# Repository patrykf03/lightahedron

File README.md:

# Lightahedron
This is the project files for the Lightahedron which is a wireless rgb tetrahedron made from fr4 panels and a 3d printed frame.

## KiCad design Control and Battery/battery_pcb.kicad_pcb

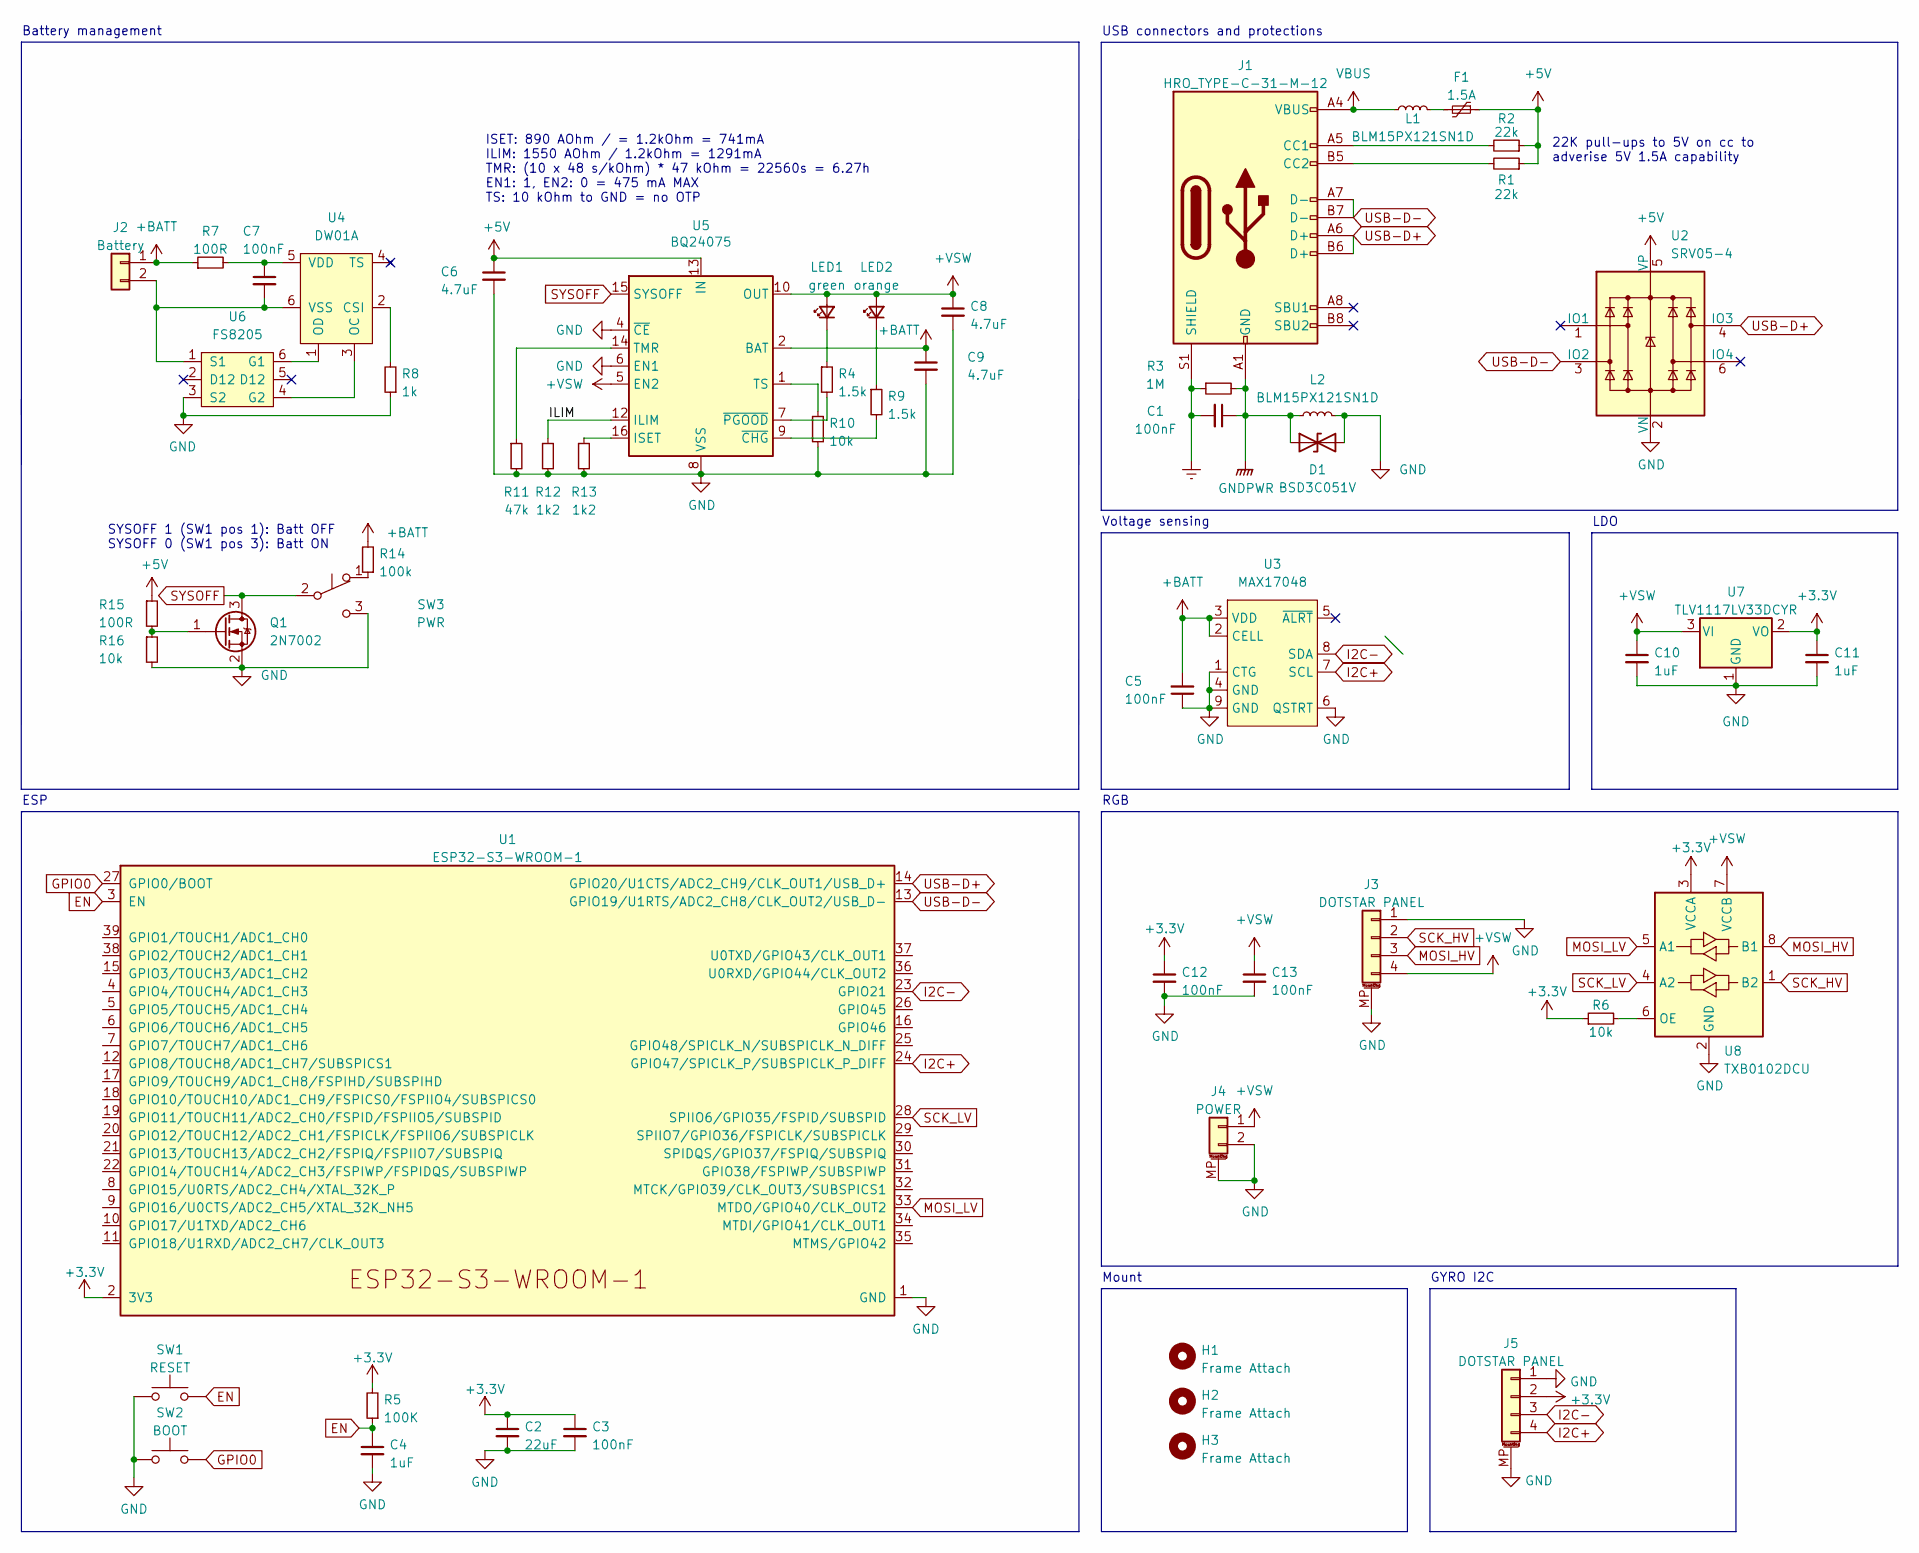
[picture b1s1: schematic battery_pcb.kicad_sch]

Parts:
C1, C3, C7, C12, C13: 100nF; C_0402_1005Metric
C2: 22uF; C_0402_1005Metric
C4, C10, C11: 1uF; C_0402_1005Metric
C5: 100nF; C_0402_1005Metric; LCSC C52923
C6, C8, C9: 4.7uF; C_0402_1005Metric
D1: BSD3C051V; D_SOD-323
F1: 1.5A; Fuse_1206_3216Metric
H1, H2, H3: Frame Attach; MountingHole_2.2mm_M2_ISO7380_Pad
J1: HRO_TYPE-C-31-M-12; USB_C_Receptacle_HRO_TYPE-C-31-M-12
J2: Battery; Keystone 18350 clips
J3, J5: DOTSTAR PANEL; JST_SH_BM04B-SRSS-TB_1x04-1MP_P1.00mm_Vertical
J4: POWER; JST_SH_BM02B-SRSS-TB_1x02-1MP_P1.00mm_Vertical
L1, L2: BLM15PX121SN1D; L_0402_1005Metric
LED1: green; LED_0402_1005Metric
LED2: orange; LED_0402_1005Metric
Q1: 2N7002; SOT-23
R1, R2: 22k; R_0402_1005Metric
R3: 1M; R_0402_1005Metric
R4, R9: 1.5k; R_0402_1005Metric
R5: 100K; R_0402_1005Metric
R6, R10, R16: 10k; R_0402_1005Metric
R7, R15: 100R; R_0402_1005Metric
R8: 1k; R_0402_1005Metric
R11: 47k; R_0402_1005Metric
R12, R13: 1k2; R_0402_1005Metric
R14: 100k; R_0402_1005Metric
SW1: RESET; SW_SPST_SKQG_WithStem
SW2: BOOT; SW_SPST_SKQG_WithStem
SW3: PWR; SW_SSSS213100
U1: ESP32-S3-WROOM-1
U2: SRV05-4; SOT-23-6-routable
U3: MAX17048; DFN-8-1EP_2x2mm_P0.5mm_EP0.7x1.3mm
U4: DW01A; SOT-23-6; LCSC C61503
U5: BQ24075; VQFN-16-1EP_3x3mm_P0.5mm_EP1.6x1.6mm
U6: FS8205; SOT-23-6; LCSC C32254
U7: TLV1117LV33DCYR; SOT-223-3_TabPin2
U8: TXB0102DCU; VSSOP-8_2.4x2.1mm_P0.5mm

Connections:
+3.3V: C2.1, C3.1, C11.1, C12.1, J5.2, R5.2, R6.1, U1.2 (3V3), U7.2 (VO), U8.3 (VCCA)
+5V: C6.1, F1.1, R1.1, R2.1, R15.1, U2.5 (VP), U5.13 (IN)
+BATT: C5.2, C9.1, J2.1, R7.1, R14.2, U3.2 (CELL), U3.3 (VDD), U5.2 (BAT), U5.3 (BAT)
+VSW: C8.1, C10.1, C13.1, J3.4, J4.1, LED1.2 (A), LED2.2 (A), U5.5 (EN2), U5.10 (OUT), U5.11 (OUT), U7.3 (VI), U8.7 (VCCB)
/ILIM: R12.1, U5.12 (ILIM)
EN: C4.1, R5.1, SW1.2, U1.3 (EN)
Earth: C1.2, J1.S1 (SHIELD), R3.1
GND: C2.2, C3.2, C4.2, C5.1, C6.2, C8.2, C9.2, C10.2, C11.2, C12.2, C13.2, D1.2 (A2), J3.1, J3.MP (MountPin), J4.2, J4.MP (MountPin), J5.1, J5.MP (MountPin), L2.2, Q1.2 (S), R8.1, R10.2, R11.2, R12.2, R13.2, R16.2, SW1.1, SW2.1, SW3.3 (C), U1.1 (GND), U1.40 (GND), U1.41 (GND), U2.2 (VN), U3.1 (CTG), U3.4 (GND), U3.6 (QSTRT), U3.9 (GND), U5.4 (~CE), U5.6 (EN1), U5.8 (VSS), U5.17 (VSS), U6.3 (S2), U7.1 (GND), U8.2 (GND)
GNDPWR: C1.1, D1.1 (A1), J1.A1 (GND), J1.A12 (GND), J1.B1 (GND), J1.B12 (GND), L2.1, R3.2
GPIO0: SW2.2, U1.27 (GPIO0/BOOT)
I2C+: J5.4, U1.24 (GPIO47/SPICLK_P/SUBSPICLK_P_DIFF), U3.7 (SCL)
I2C-: J5.3, U1.23 (GPIO21), U3.8 (SDA)
MOSI_HV: J3.3, U8.8 (B1)
MOSI_LV: U1.33 (MTDO/GPIO40/CLK_OUT2), U8.5 (A1)
unnamed: C7.1, R7.2, U4.5 (VDD)
unnamed: C7.2, J2.2, U4.6 (VSS), U6.1 (S1)
unnamed: F1.2, L1.2
unnamed: J1.A5 (CC1), R2.2
unnamed: J1.B5 (CC2), R1.2
unnamed: LED1.1 (K), R4.1
unnamed: LED2.1 (K), R9.1
unnamed: Q1.1 (G), R15.2, R16.1
unnamed: R4.2, U5.7 (~PGOOD)
unnamed: R6.2, U8.6 (OE)
unnamed: R8.2, U4.2 (CSI)
unnamed: R9.2, U5.9 (~CHG)
unnamed: R10.1, U5.1 (TS)
unnamed: R11.1, U5.14 (TMR)
unnamed: R13.1, U5.16 (ISET)
unnamed: R14.1, SW3.1 (A)
unnamed: U4.1 (OD), U6.6 (G1)
unnamed: U4.3 (OC), U6.4 (G2)
SCK_HV: J3.2, U8.1 (B2)
SCK_LV: U1.28 (SPIIO6/GPIO35/FSPID/SUBSPID), U8.4 (A2)
SYSOFF: Q1.3 (D), SW3.2 (B), U5.15 (SYSOFF)
USB-D+: J1.A6 (D+), J1.B6 (D+), U1.14 (GPIO20/U1CTS/ADC2_CH9/CLK_OUT1/USB_D+), U2.4 (IO3)
USB-D-: J1.A7 (D-), J1.B7 (D-), U1.13 (GPIO19/U1RTS/ADC2_CH8/CLK_OUT2/USB_D-), U2.3 (IO2)
VBUS: J1.A4 (VBUS), J1.A9 (VBUS), J1.B4 (VBUS), J1.B9 (VBUS), L1.1

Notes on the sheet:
Voltage sensing
ISET: 890 AOhm / = 1.2kOhm = 741mA ILIM: 1550 AOhm / 1.2kOhm = 1291mA TMR: (10 x 48 s/kOhm) * 47 kOhm = 22560s = 6.27h EN1: 1, EN2: 0 = 475 mA MAX TS: 10 kOhm to GND = no OTP
GYRO I2C
Battery management
Mount
ESP
22K pull-ups to 5V on cc to adverise 5V 1.5A capability
RGB
LDO
SYSOFF 1 (SW1 pos 1): Batt OFF SYSOFF 0 (SW1 pos 3): Batt ON
USB connectors and protections

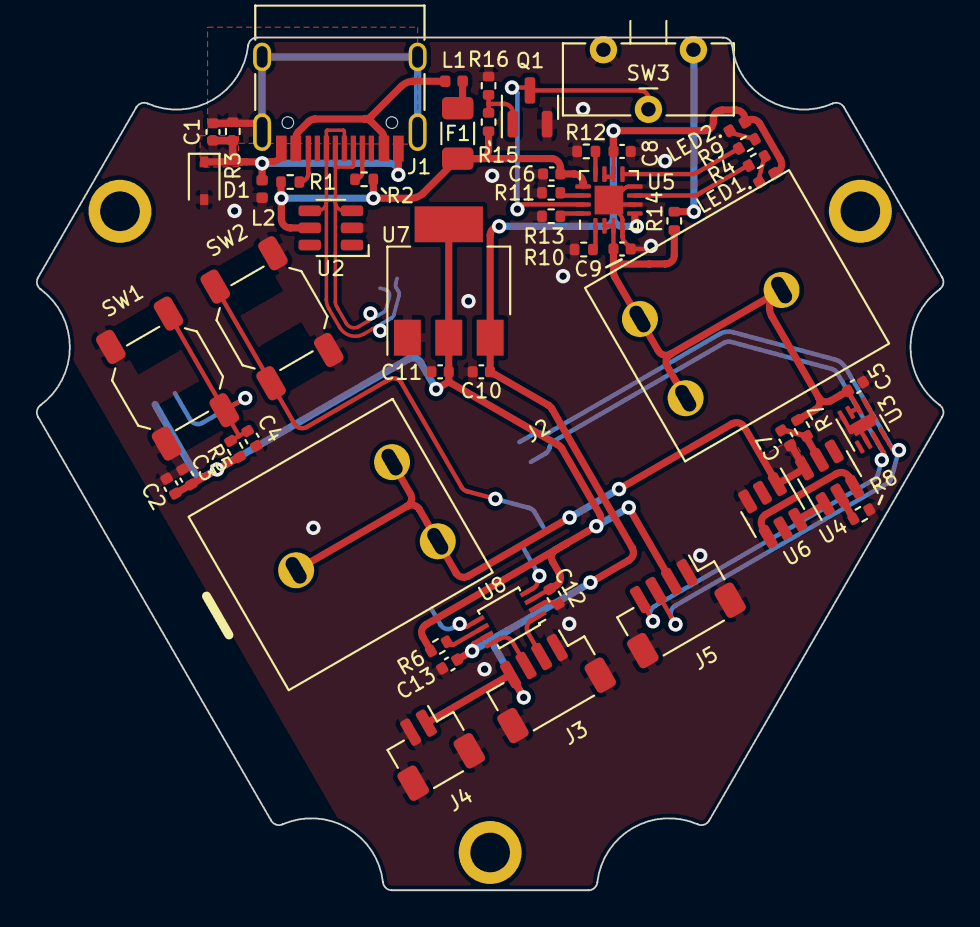
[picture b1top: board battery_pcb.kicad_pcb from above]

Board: 2 copper layers, 50.4 x 47.4 mm, 55 parts (1 on the bottom side), 38 nets.

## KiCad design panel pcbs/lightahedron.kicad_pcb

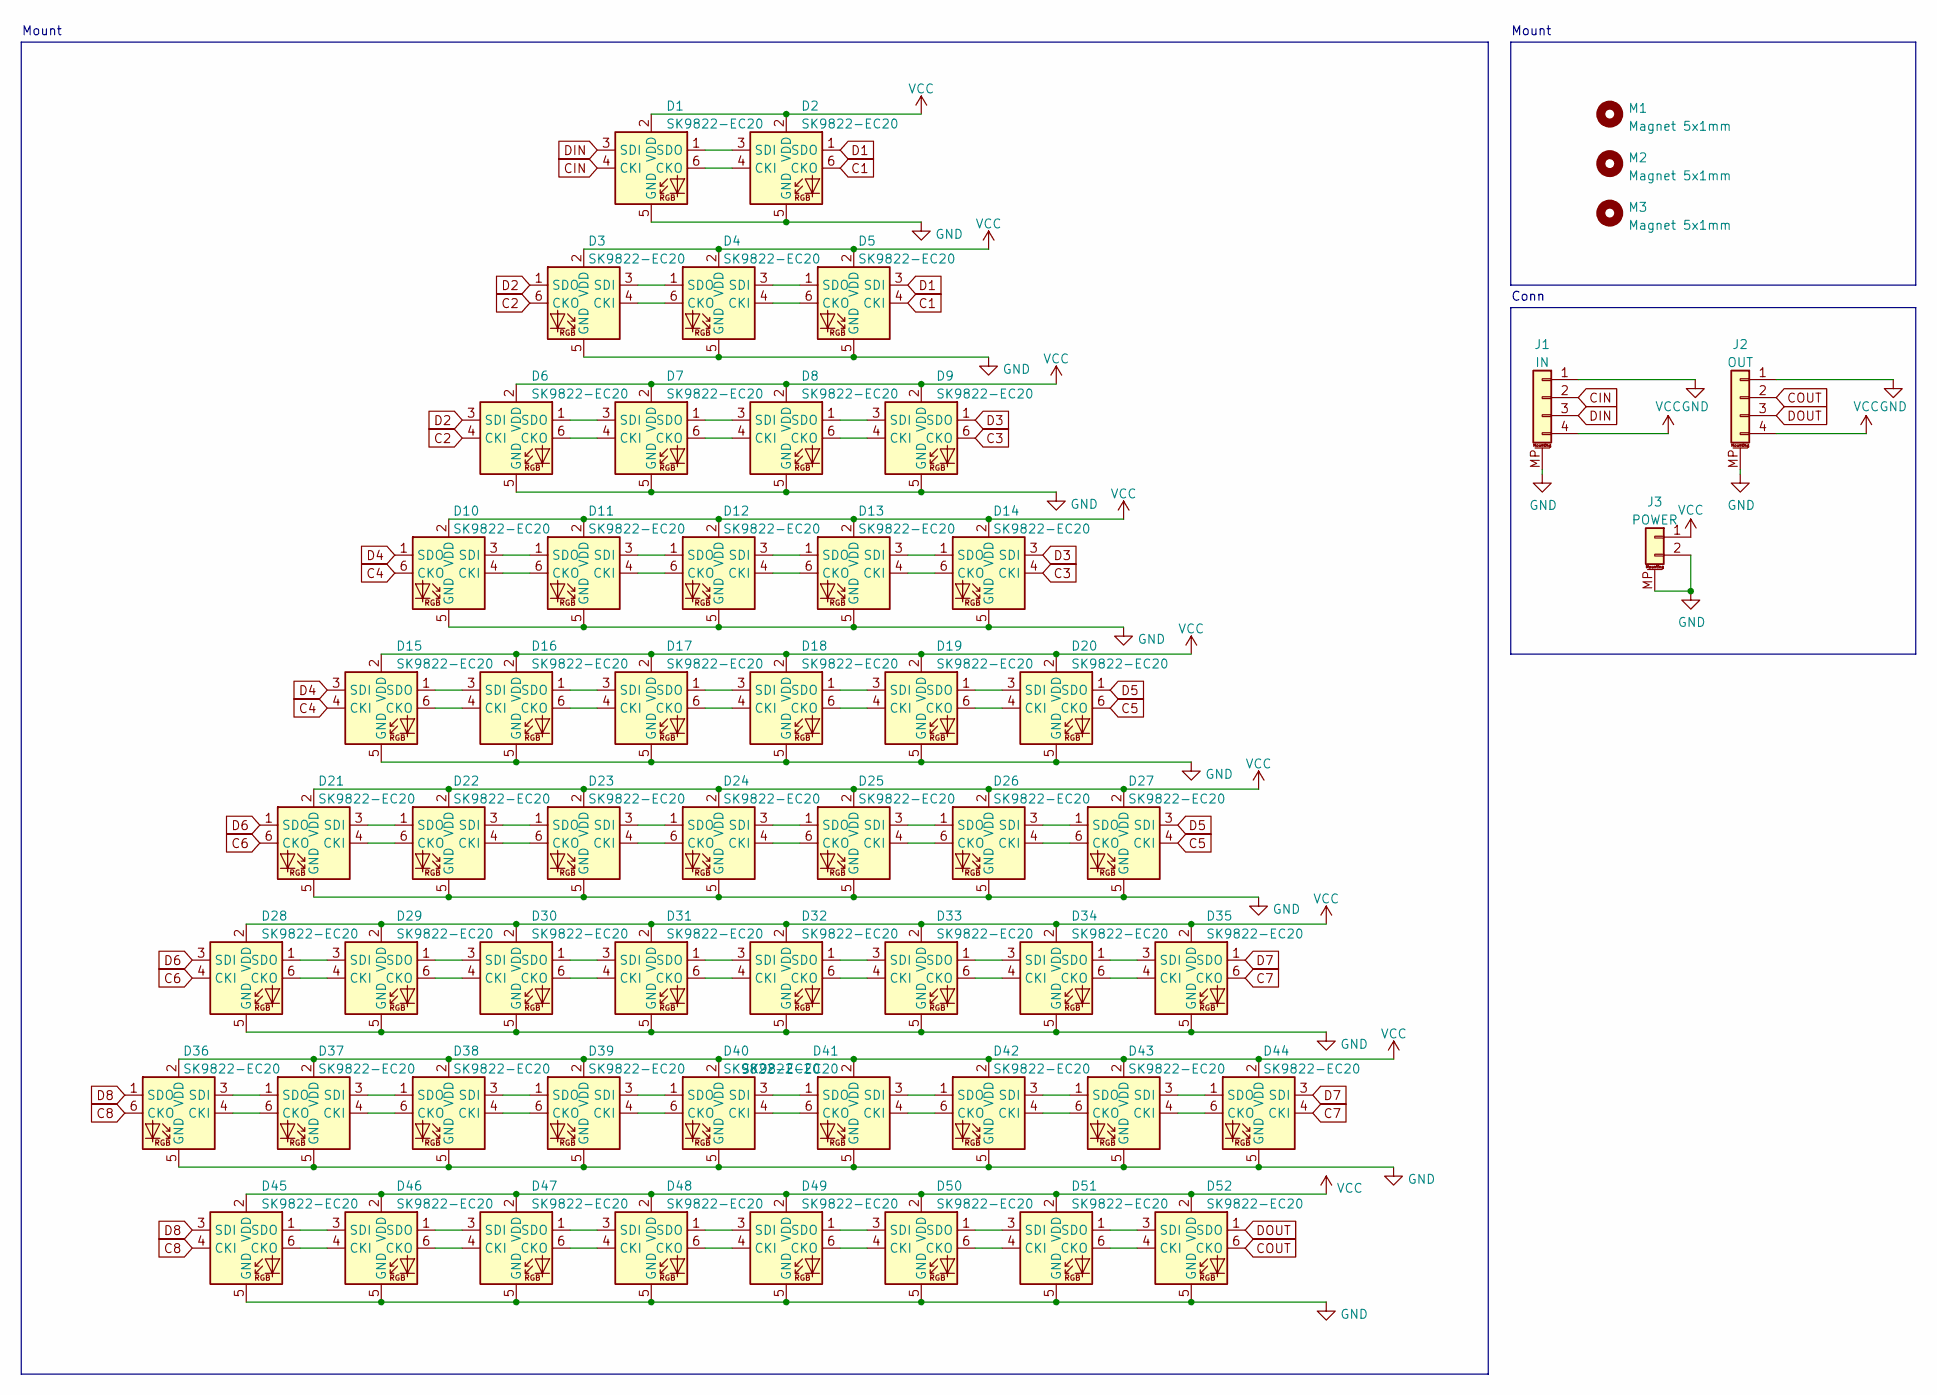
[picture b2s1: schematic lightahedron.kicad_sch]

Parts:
D1, D2, D3, D4, D5, D6, D7, D8, D9, D10, D11, D12, D13, D14, D15, D16, D17, D18, D19, D20, D21, D22, D23, D24, D25, D26, D27, D28, D29, D30, D31, D32, D33, D34, D35, D36, D37, D38, D39, D40, D41, D42, D43, D44, D45, D46, D47, D48, D49, D50, D51, D52: SK9822-EC20; sk9822-2020
J1: IN; JST_SH_SM04B-SRSS-TB_1x04-1MP_P1.00mm_Horizontal
J2: OUT; JST_SH_SM04B-SRSS-TB_1x04-1MP_P1.00mm_Horizontal
J3: POWER; JST_SH_SM02B-SRSS-TB_1x02-1MP_P1.00mm_Horizontal
M1, M2, M3: Magnet 5x1mm; Magnet_D5mm_L2mm

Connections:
C1: D2.6 (CKO), D5.4 (CKI)
C2: D3.6 (CKO), D6.4 (CKI)
C3: D9.6 (CKO), D14.4 (CKI)
C4: D10.6 (CKO), D15.4 (CKI)
C5: D20.6 (CKO), D27.4 (CKI)
C6: D21.6 (CKO), D28.4 (CKI)
C7: D35.6 (CKO), D44.4 (CKI)
C8: D36.6 (CKO), D45.4 (CKI)
CIN: D1.4 (CKI), J1.2
COUT: D52.6 (CKO), J2.2
D1: D2.1 (SDO), D5.3 (SDI)
D2: D3.1 (SDO), D6.3 (SDI)
D3: D9.1 (SDO), D14.3 (SDI)
D4: D10.1 (SDO), D15.3 (SDI)
D5: D20.1 (SDO), D27.3 (SDI)
D6: D21.1 (SDO), D28.3 (SDI)
D7: D35.1 (SDO), D44.3 (SDI)
D8: D36.1 (SDO), D45.3 (SDI)
DIN: D1.3 (SDI), J1.3
DOUT: D52.1 (SDO), J2.3
GND: D1.5 (GND), D2.5 (GND), D3.5 (GND), D4.5 (GND), D5.5 (GND), D6.5 (GND), D7.5 (GND), D8.5 (GND), D9.5 (GND), D10.5 (GND), D11.5 (GND), D12.5 (GND), D13.5 (GND), D14.5 (GND), D15.5 (GND), D16.5 (GND), D17.5 (GND), D18.5 (GND), D19.5 (GND), D20.5 (GND), D21.5 (GND), D22.5 (GND), D23.5 (GND), D24.5 (GND), D25.5 (GND), D26.5 (GND), D27.5 (GND), D28.5 (GND), D29.5 (GND), D30.5 (GND), D31.5 (GND), D32.5 (GND), D33.5 (GND), D34.5 (GND), D35.5 (GND), D36.5 (GND), D37.5 (GND), D38.5 (GND), D39.5 (GND), D40.5 (GND), D41.5 (GND), D42.5 (GND), D43.5 (GND), D44.5 (GND), D45.5 (GND), D46.5 (GND), D47.5 (GND), D48.5 (GND), D49.5 (GND), D50.5 (GND), D51.5 (GND), D52.5 (GND), J1.1, J1.MP (MountPin), J2.1, J2.MP (MountPin), J3.2, J3.MP (MountPin)
unnamed: D1.1 (SDO), D2.3 (SDI)
unnamed: D1.6 (CKO), D2.4 (CKI)
unnamed: D3.3 (SDI), D4.1 (SDO)
unnamed: D3.4 (CKI), D4.6 (CKO)
unnamed: D4.3 (SDI), D5.1 (SDO)
unnamed: D4.4 (CKI), D5.6 (CKO)
unnamed: D6.1 (SDO), D7.3 (SDI)
unnamed: D6.6 (CKO), D7.4 (CKI)
unnamed: D7.1 (SDO), D8.3 (SDI)
unnamed: D7.6 (CKO), D8.4 (CKI)
unnamed: D8.1 (SDO), D9.3 (SDI)
unnamed: D8.6 (CKO), D9.4 (CKI)
unnamed: D10.3 (SDI), D11.1 (SDO)
unnamed: D10.4 (CKI), D11.6 (CKO)
unnamed: D11.3 (SDI), D12.1 (SDO)
unnamed: D11.4 (CKI), D12.6 (CKO)
unnamed: D12.3 (SDI), D13.1 (SDO)
unnamed: D12.4 (CKI), D13.6 (CKO)
unnamed: D13.3 (SDI), D14.1 (SDO)
unnamed: D13.4 (CKI), D14.6 (CKO)
unnamed: D15.1 (SDO), D16.3 (SDI)
unnamed: D15.6 (CKO), D16.4 (CKI)
unnamed: D16.1 (SDO), D17.3 (SDI)
unnamed: D16.6 (CKO), D17.4 (CKI)
unnamed: D17.1 (SDO), D18.3 (SDI)
unnamed: D17.6 (CKO), D18.4 (CKI)
unnamed: D18.1 (SDO), D19.3 (SDI)
unnamed: D18.6 (CKO), D19.4 (CKI)
unnamed: D19.1 (SDO), D20.3 (SDI)
unnamed: D19.6 (CKO), D20.4 (CKI)
unnamed: D21.3 (SDI), D22.1 (SDO)
unnamed: D21.4 (CKI), D22.6 (CKO)
unnamed: D22.3 (SDI), D23.1 (SDO)
unnamed: D22.4 (CKI), D23.6 (CKO)
unnamed: D23.3 (SDI), D24.1 (SDO)
unnamed: D23.4 (CKI), D24.6 (CKO)
unnamed: D24.3 (SDI), D25.1 (SDO)
unnamed: D24.4 (CKI), D25.6 (CKO)
unnamed: D25.3 (SDI), D26.1 (SDO)
unnamed: D25.4 (CKI), D26.6 (CKO)
unnamed: D26.3 (SDI), D27.1 (SDO)
unnamed: D26.4 (CKI), D27.6 (CKO)
unnamed: D28.1 (SDO), D29.3 (SDI)
unnamed: D28.6 (CKO), D29.4 (CKI)
unnamed: D29.1 (SDO), D30.3 (SDI)
unnamed: D29.6 (CKO), D30.4 (CKI)
unnamed: D30.1 (SDO), D31.3 (SDI)
unnamed: D30.6 (CKO), D31.4 (CKI)
unnamed: D31.1 (SDO), D32.3 (SDI)
unnamed: D31.6 (CKO), D32.4 (CKI)
unnamed: D32.1 (SDO), D33.3 (SDI)
unnamed: D32.6 (CKO), D33.4 (CKI)
unnamed: D33.1 (SDO), D34.3 (SDI)
unnamed: D33.6 (CKO), D34.4 (CKI)
unnamed: D34.1 (SDO), D35.3 (SDI)
unnamed: D34.6 (CKO), D35.4 (CKI)
unnamed: D36.3 (SDI), D37.1 (SDO)
unnamed: D36.4 (CKI), D37.6 (CKO)
unnamed: D37.3 (SDI), D38.1 (SDO)
unnamed: D37.4 (CKI), D38.6 (CKO)
unnamed: D38.3 (SDI), D39.1 (SDO)
unnamed: D38.4 (CKI), D39.6 (CKO)
unnamed: D39.3 (SDI), D40.1 (SDO)
unnamed: D39.4 (CKI), D40.6 (CKO)
unnamed: D40.3 (SDI), D41.1 (SDO)
unnamed: D40.4 (CKI), D41.6 (CKO)
unnamed: D41.3 (SDI), D42.1 (SDO)
unnamed: D41.4 (CKI), D42.6 (CKO)
unnamed: D42.3 (SDI), D43.1 (SDO)
unnamed: D42.4 (CKI), D43.6 (CKO)
unnamed: D43.3 (SDI), D44.1 (SDO)
unnamed: D43.4 (CKI), D44.6 (CKO)
unnamed: D45.1 (SDO), D46.3 (SDI)
unnamed: D45.6 (CKO), D46.4 (CKI)
unnamed: D46.1 (SDO), D47.3 (SDI)
unnamed: D46.6 (CKO), D47.4 (CKI)
unnamed: D47.1 (SDO), D48.3 (SDI)
unnamed: D47.6 (CKO), D48.4 (CKI)
unnamed: D48.1 (SDO), D49.3 (SDI)
unnamed: D48.6 (CKO), D49.4 (CKI)
unnamed: D49.1 (SDO), D50.3 (SDI)
unnamed: D49.6 (CKO), D50.4 (CKI)
unnamed: D50.1 (SDO), D51.3 (SDI)
unnamed: D50.6 (CKO), D51.4 (CKI)
unnamed: D51.1 (SDO), D52.3 (SDI)
unnamed: D51.6 (CKO), D52.4 (CKI)
VCC: D1.2 (VDD), D2.2 (VDD), D3.2 (VDD), D4.2 (VDD), D5.2 (VDD), D6.2 (VDD), D7.2 (VDD), D8.2 (VDD), D9.2 (VDD), D10.2 (VDD), D11.2 (VDD), D12.2 (VDD), D13.2 (VDD), D14.2 (VDD), D15.2 (VDD), D16.2 (VDD), D17.2 (VDD), D18.2 (VDD), D19.2 (VDD), D20.2 (VDD), D21.2 (VDD), D22.2 (VDD), D23.2 (VDD), D24.2 (VDD), D25.2 (VDD), D26.2 (VDD), D27.2 (VDD), D28.2 (VDD), D29.2 (VDD), D30.2 (VDD), D31.2 (VDD), D32.2 (VDD), D33.2 (VDD), D34.2 (VDD), D35.2 (VDD), D36.2 (VDD), D37.2 (VDD), D38.2 (VDD), D39.2 (VDD), D40.2 (VDD), D41.2 (VDD), D42.2 (VDD), D43.2 (VDD), D44.2 (VDD), D45.2 (VDD), D46.2 (VDD), D47.2 (VDD), D48.2 (VDD), D49.2 (VDD), D50.2 (VDD), D51.2 (VDD), D52.2 (VDD), J1.4, J2.4, J3.1

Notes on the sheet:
Mount
Conn

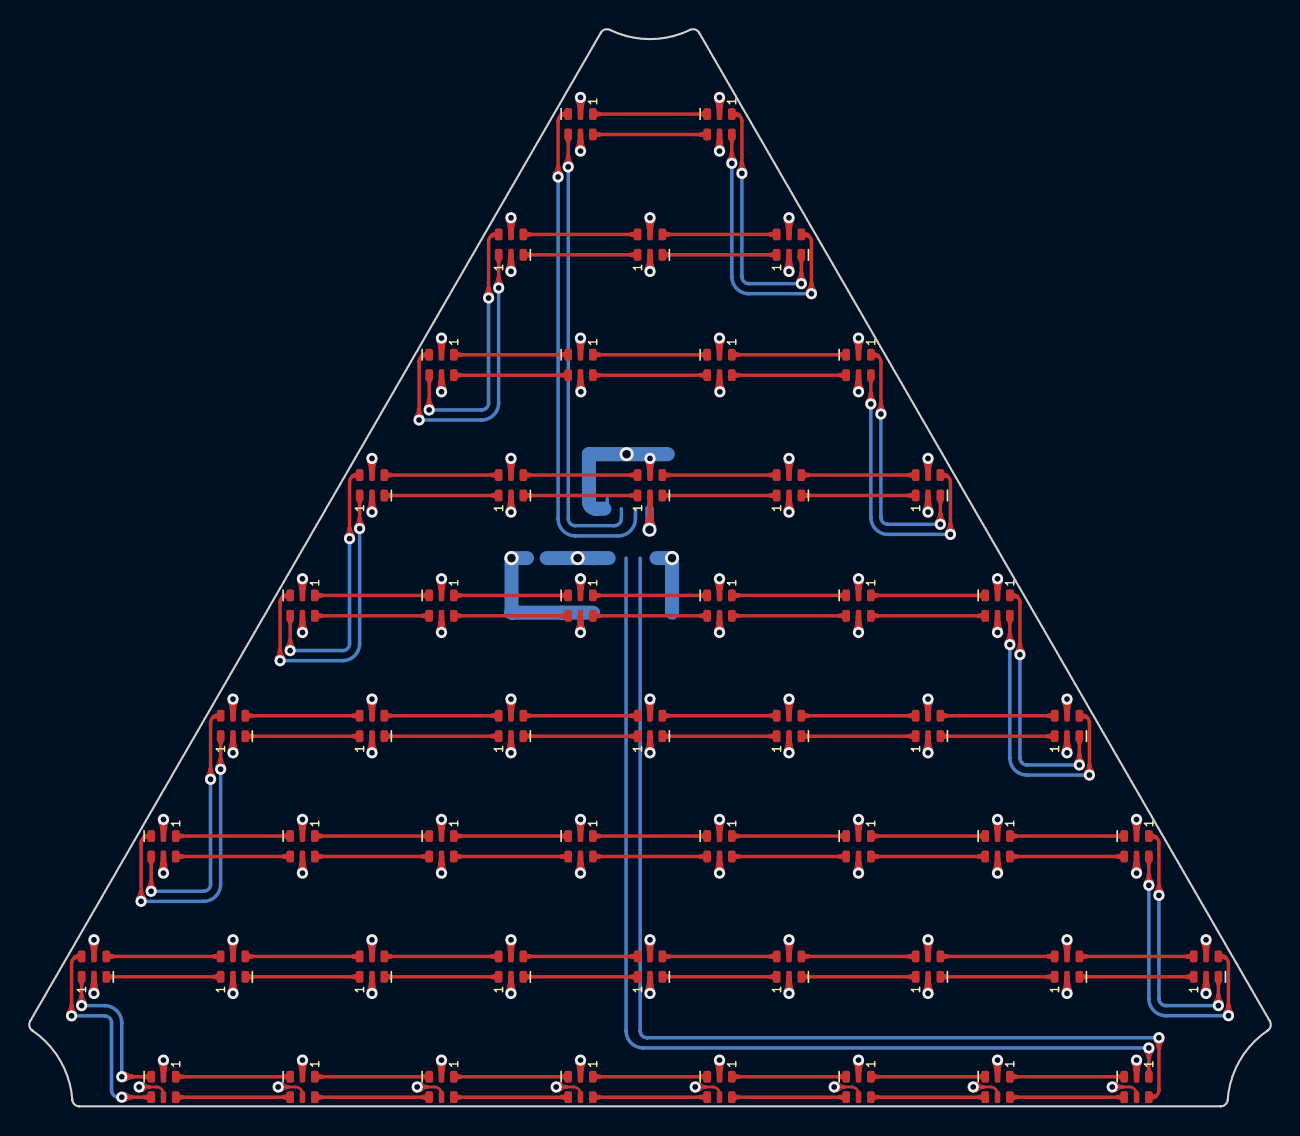
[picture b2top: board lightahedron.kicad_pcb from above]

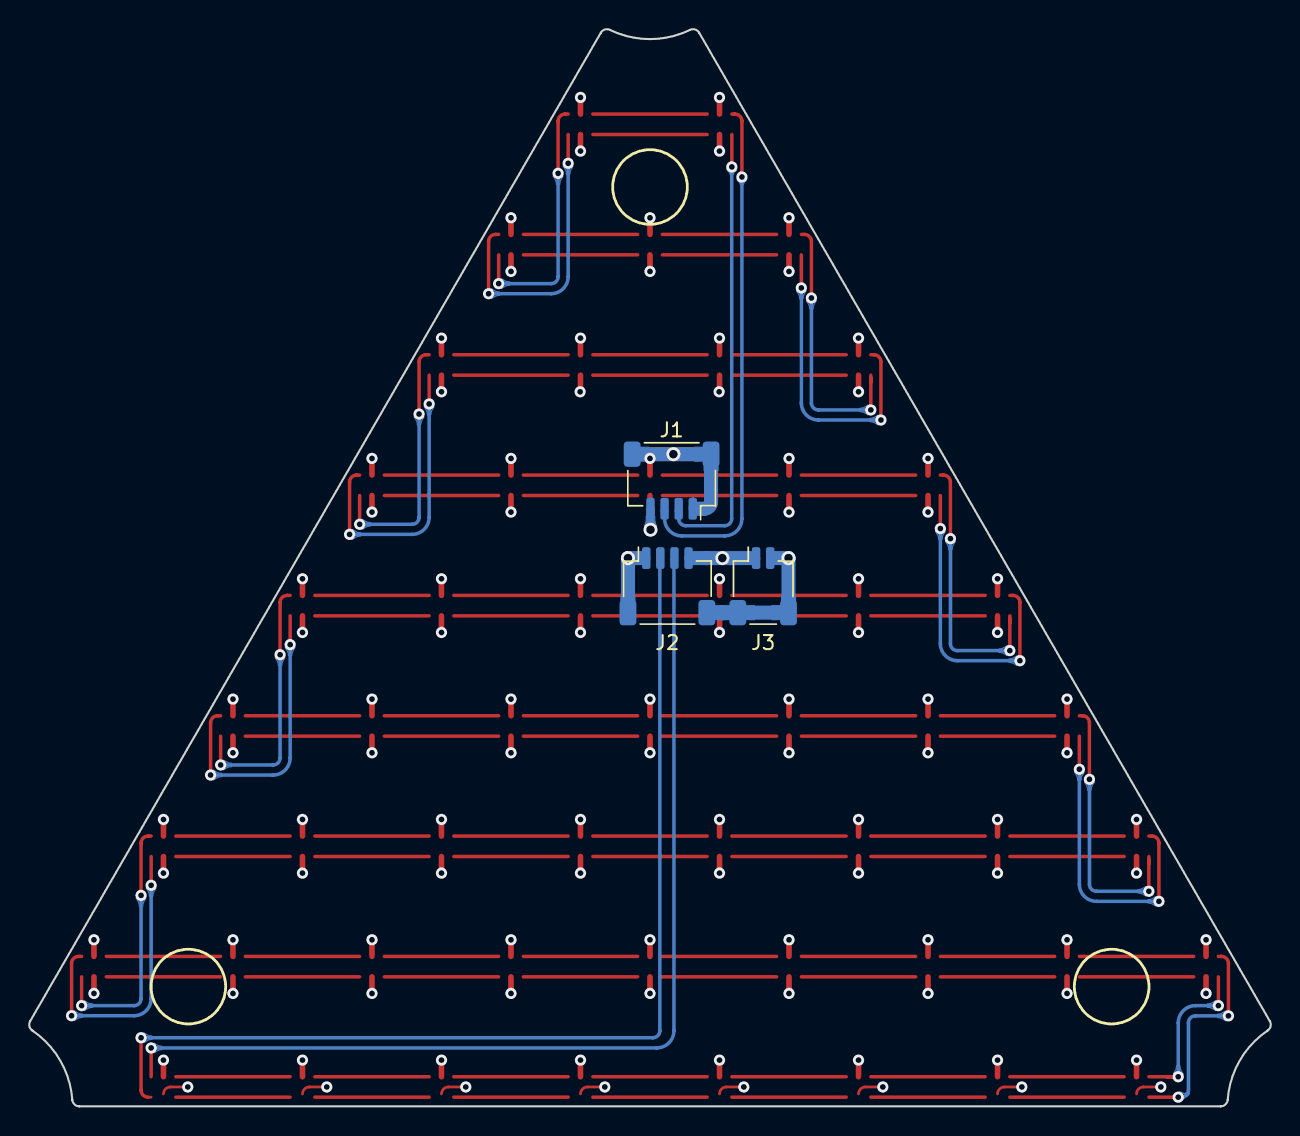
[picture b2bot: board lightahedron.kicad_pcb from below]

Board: 4 copper layers, 88.2 x 76.5 mm, 58 parts (6 on the bottom side), 108 nets.

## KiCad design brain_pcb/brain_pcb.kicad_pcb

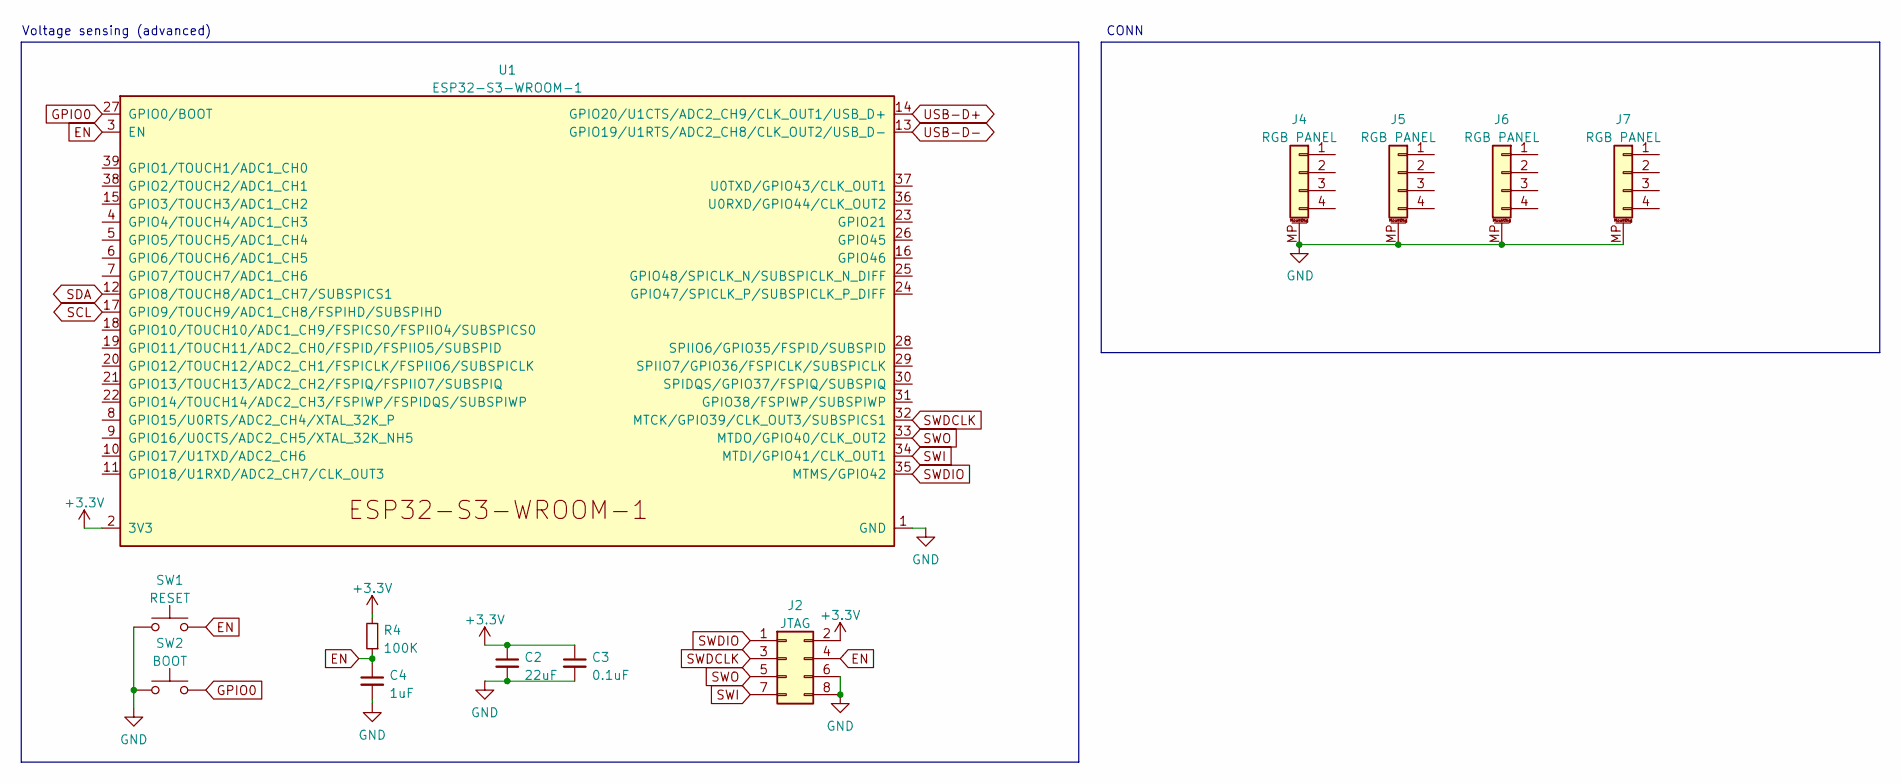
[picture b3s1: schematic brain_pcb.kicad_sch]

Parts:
C2: 22uF; C_0402_1005Metric
C3: 0.1uF; C_0402_1005Metric
C4: 1uF; C_0402_1005Metric
J2: JTAG; PinSocket_2x04_P2.54mm_Vertical
J4, J5, J6, J7: RGB PANEL; JST_SH_SM04B-SRSS-TB_1x04-1MP_P1.00mm_Horizontal
R4: 100K; R_0402_1005Metric
SW1: RESET; SW_Tactile_SPST_Angled_PTS645Vx39-2LFS
SW2: BOOT; SW_Tactile_SPST_Angled_PTS645Vx39-2LFS
U1: ESP32-S3-WROOM-1; ESP32-S3-WROOM-1U

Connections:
+3.3V: C2.1, C3.1, J2.2, R4.2, U1.2 (3V3)
EN: C4.1, J2.4, R4.1, SW1.2, U1.3 (EN)
GND: C2.2, C3.2, C4.2, J2.6, J2.8, J4.MP (MountPin), J5.MP (MountPin), J6.MP (MountPin), J7.MP (MountPin), SW1.1, SW2.1, U1.1 (GND), U1.40 (GND), U1.41 (GND)
GPIO0: SW2.2, U1.27 (GPIO0/BOOT)
SCL: U1.17 (GPIO9/TOUCH9/ADC1_CH8/FSPIHD/SUBSPIHD)
SDA: U1.12 (GPIO8/TOUCH8/ADC1_CH7/SUBSPICS1)
SWDCLK: J2.3, U1.32 (MTCK/GPIO39/CLK_OUT3/SUBSPICS1)
SWDIO: J2.1, U1.35 (MTMS/GPIO42)
SWI: J2.7, U1.34 (MTDI/GPIO41/CLK_OUT1)
SWO: J2.5, U1.33 (MTDO/GPIO40/CLK_OUT2)
USB-D+: U1.14 (GPIO20/U1CTS/ADC2_CH9/CLK_OUT1/USB_D+)
USB-D-: U1.13 (GPIO19/U1RTS/ADC2_CH8/CLK_OUT2/USB_D-)

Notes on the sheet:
CONN
Voltage sensing (advanced)

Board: 2 copper layers, 12 parts (0 on the bottom side), 8 nets, no tracks yet.

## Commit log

2023-01-17 add files
2023-01-20 cleanup and work on pcb and cad
2023-01-27 cleanup, work on pcbs, finish frame, add render
2023-01-27 add license
